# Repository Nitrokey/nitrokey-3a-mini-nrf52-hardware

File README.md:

# Nitrokey 3A Mini and Nitrokey Passkey Hardware

The hardware files of [Nitrokey 3A Mini](https://shop.nitrokey.com/shop/nk3am-nitrokey-3a-mini-149) and [Nitrokey Passkey](https://shop.nitrokey.com/shop/nkpk-nitrokey-passkey-418).
The firmware is [here](https://github.com/Nitrokey/nitrokey-3-firmware).

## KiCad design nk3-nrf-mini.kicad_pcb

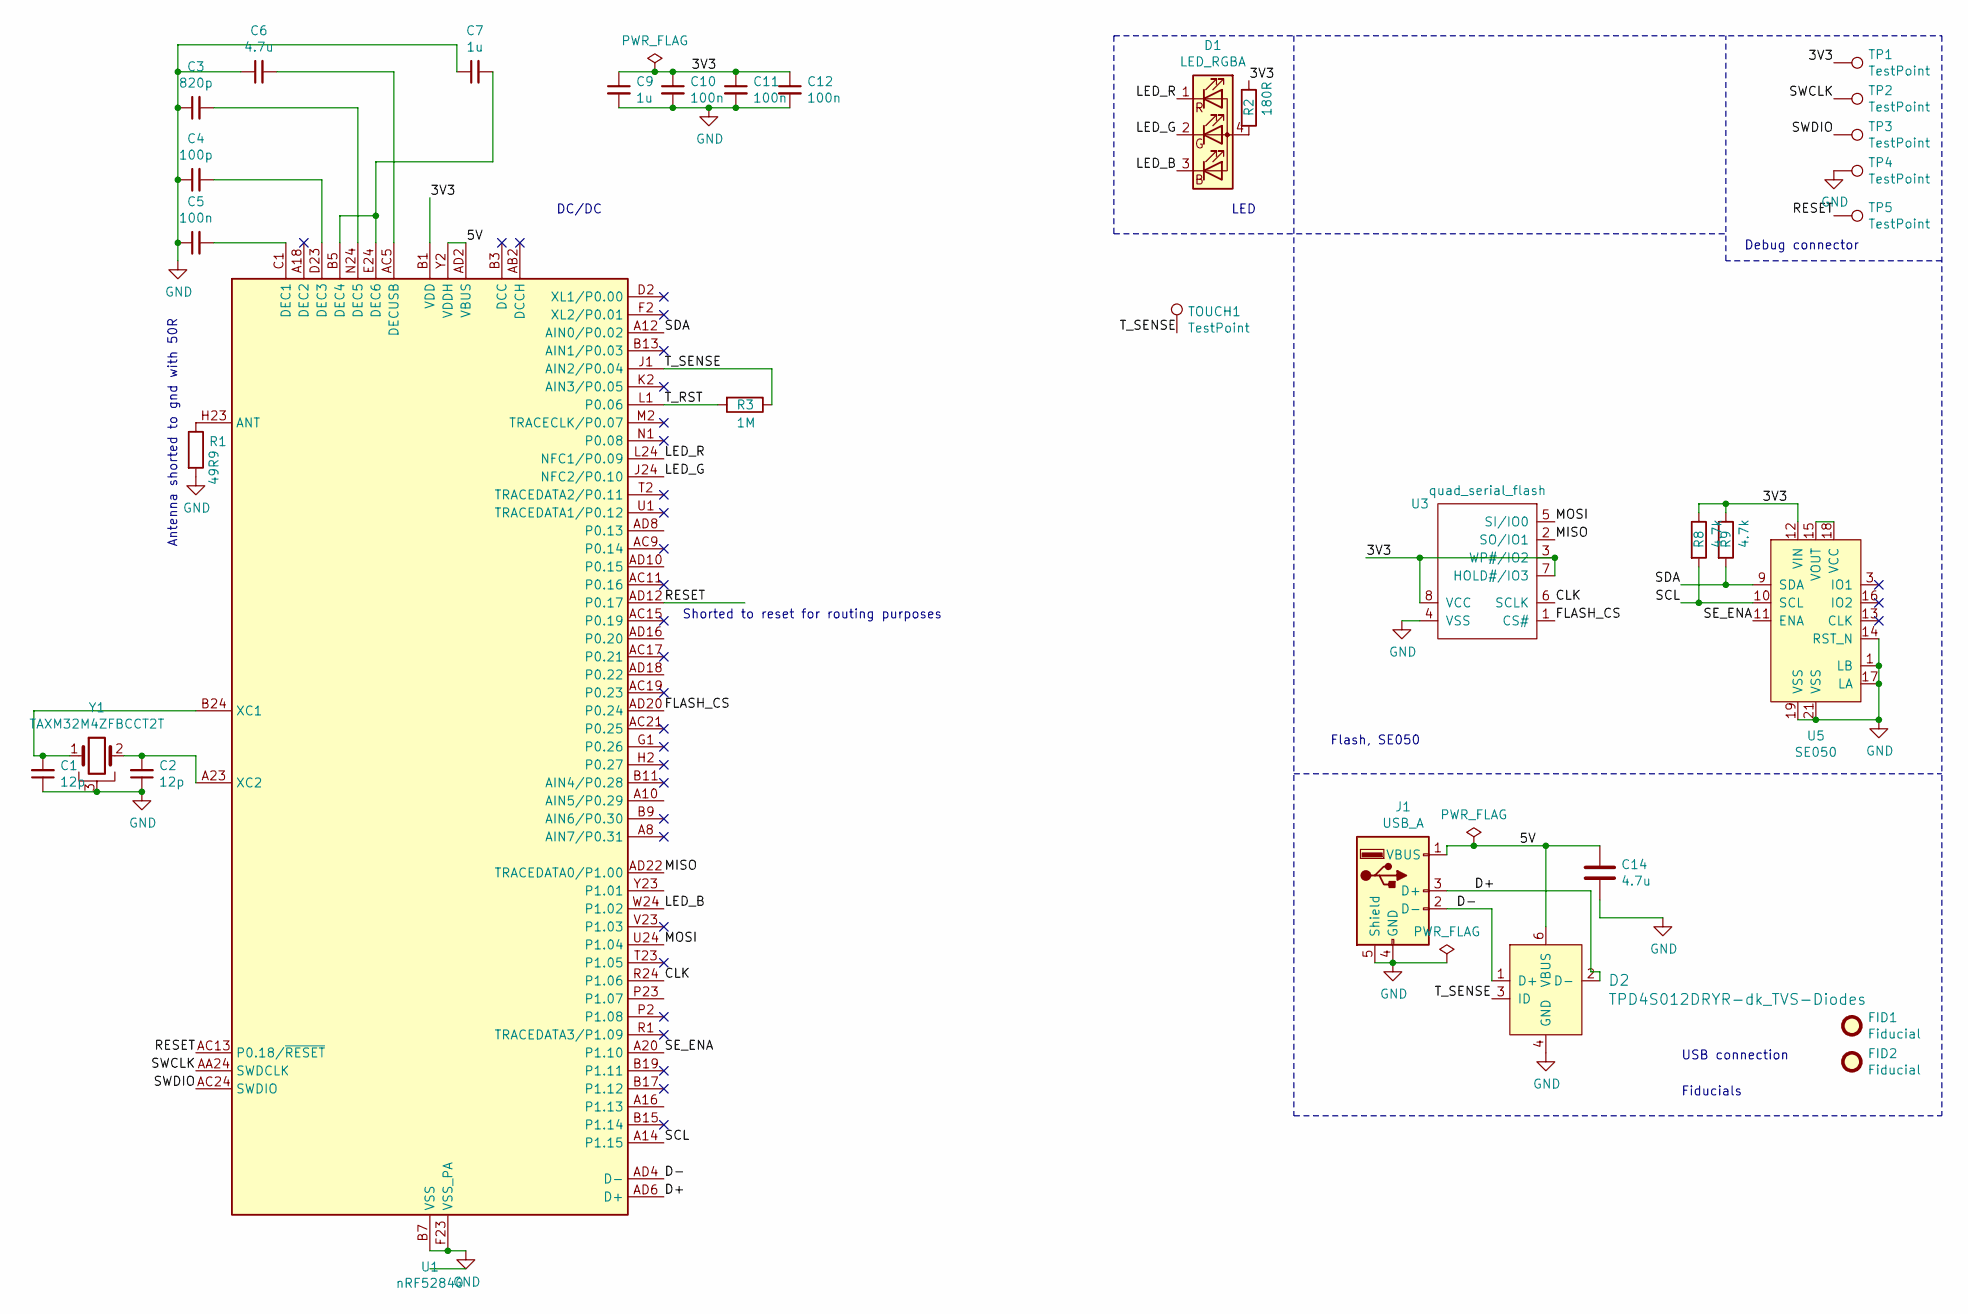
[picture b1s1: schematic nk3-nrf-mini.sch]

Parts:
C1, C2: 12p; C_0201_0603Metric
C3: 820p; C_0201_0603Metric
C4: 100p; C_0201_0603Metric
C5, C10, C11, C12: 100n; C_0201_0603Metric
C6, C14: 4.7u; C_0402_1005Metric
C7, C9: 1u; C_0402_1005Metric
D1: LED_RGBA; RGB_LED_606
D2: TPD4S012DRYR-dk_TVS-Diodes; UFDFN-6_1.45x1mm; MPN TPD4S012DRYR; Digi-Key_PN 296-24244-1-ND
FID1, FID2: Fiducial; Fiducial_0.5mm_Mask1mm
J1: USB_A; usb-a-pattern
R1: 49R9; R_0201_0603Metric
R2: 180R; R_0201_0603Metric
R3: 1M; R_0201_0603Metric
R8, R9: 4.7k; R_0201_0603Metric
TOUCH1: TestPoint; touchpad-curve
TP1, TP2, TP3, TP4, TP5: TestPoint; TestPoint_Pad_D1.5mm
U1: nRF52840; Nordic_AQFN-73-1EP_7x7mm_P0.5mm
U3: quad_serial_flash; FLASH_2x3_USON8
U5: SE050; UQFN-20-1EP_3x3mm_P0.4mm_EP1.85x1.85mm
Y1: TAXM32M4ZFBCCT2T; Crystal-2mmx1.6mm

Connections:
/3V3: C9.1, C10.1, C11.1, C12.1, R2.1, R8.1, R9.1, TP1.1, U1.A22 (VDD), U1.AD14 (VDD), U1.AD23 (VDD), U1.B1 (VDD), U1.W1 (VDD), U3.3 (WP#/IO2), U3.7 (HOLD#/IO3), U3.8 (VCC), U5.12 (VIN)
/5V: C14.1, D2.6 (VBUS), J1.1 (VBUS), U1.AD2 (VBUS), U1.Y2 (VDDH)
/CLK: U1.R24 (P1.06), U3.6 (SCLK)
/D+: D2.2 (D-), J1.3 (D+), U1.AD6 (D+)
/D-: D2.1 (D+), J1.2 (D-), U1.AD4 (D-)
/FLASH_CS: U1.AD20 (P0.24), U3.1 (CS#)
/LED_B: D1.3 (BK), U1.W24 (P1.02)
/LED_G: D1.2 (GK), U1.J24 (NFC2/P0.10)
/LED_R: D1.1 (RK), U1.L24 (NFC1/P0.09)
/MISO: U1.AD22 (TRACEDATA0/P1.00), U3.2 (SO/IO1)
/MOSI: U1.U24 (P1.04), U3.5 (SI/IO0)
/RESET: TP5.1, U1.AC13 (P0.18/~RESET), U1.AD12 (P0.17)
/SCL: R8.2, U1.A14 (P1.15), U5.10 (SCL)
/SDA: R9.2, U1.A12 (AIN0/P0.02), U5.9 (SDA)
/SE_ENA: U1.A20 (P1.10), U5.11 (ENA)
/SWCLK: TP2.1, U1.AA24 (SWDCLK)
/SWDIO: TP3.1, U1.AC24 (SWDIO)
/T_RST: R3.2, U1.L1 (P0.06)
/T_SENSE: D2.3 (ID), R3.1, TOUCH1.1, U1.J1 (AIN2/P0.04)
GND: C1.1, C2.1, C3.1, C4.1, C5.1, C6.1, C7.1, C9.2, C10.2, C11.2, C12.2, C14.2, D2.4 (GND), J1.4 (GND), J1.5 (Shield), R1.2, TP4.1, U1.B7 (VSS), U1.EP (VSS), U1.F23 (VSS_PA), U3.4 (VSS), U5.1 (LB), U5.14 (RST_N), U5.17 (LA), U5.19 (VSS), U5.21 (VSS), Y1.3
unnamed: C1.2, U1.B24 (XC1), Y1.1
unnamed: C2.2, U1.A23 (XC2), Y1.2
unnamed: C3.2, U1.N24 (DEC5)
unnamed: C4.2, U1.D23 (DEC3)
unnamed: C5.2, U1.C1 (DEC1)
unnamed: C6.2, U1.AC5 (DECUSB)
unnamed: C7.2, U1.B5 (DEC4), U1.E24 (DEC6)
unnamed: D1.4 (A), R2.2
unnamed: R1.1, U1.H23 (ANT)
unnamed: U5.15 (VOUT), U5.18 (VCC)

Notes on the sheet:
Flash, SE050
Debug connector
USB connection
LED
Antenna shorted to gnd with 50R
DC/DC
Fiducials
Shorted to reset for routing purposes

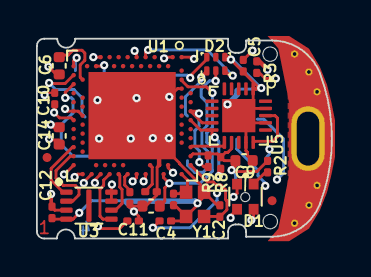
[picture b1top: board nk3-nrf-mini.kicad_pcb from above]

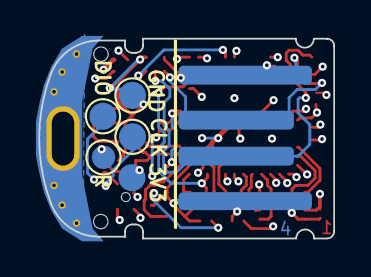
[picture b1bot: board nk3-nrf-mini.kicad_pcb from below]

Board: 4 copper layers, 16.4 x 11.1 mm, 32 parts (7 on the bottom side), 30 nets.

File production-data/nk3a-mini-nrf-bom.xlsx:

Component | Description | Part | References | Value | Footprint | Quantity Per PCB | MPN | Manufacturer
1 | C0G cap | C | C1 C2 | 12pF | C_0201_0603Metric | 2
2 | C0G cap | C | C3 | 820pF | C_0201_0603Metric | 1
3 | X5R or X7R cap, 25V | C | C5 C10 C11 C12 | 100nF | C_0201_0603Metric | 4
4 | X5R or X7R cap, 25V | C | C7 C9 | 1u | C_0402_1005Metric | 2
5 | X5R or X7R cap, 10V | C | C6 C14 | 4.7u | C_0402_1005Metric | 2
6 | C0G cap | C | C4 | 100pF | C_0201_0603Metric | 1
7 | TVS Diode | tvs diode | D2 | TPD4S012DRYR | UFDFN-6_1.45x1mm | 1 | TPD4S012DRYR | Texas Instruments
8 | SPI flash IC | spi flash | U3 | GD25Q16CEIGR | FLASH_2x3_USON8 | 1 | GD25Q16CEIGR | GigaDevice Semiconductor (HK) Limited
9 | RGB LED, red/green/blue/anode | LED_RGBA | D1 | LED_RGBA | RGB_LED_606 | 1 | 150066M153000 | Würth
10 | Resistor 1% | R | R1 | 49R9 | R_0201_0603Metric | 1
11 | Resistor 1% | R | R2 | 180R | R_0201_0603Metric | 1
12 | Resistor 1% | R | R3 | 1M | R_0201_0603Metric | 1
13 | Resistor 1% | R | R8 R9 | 4.7k | R_0201_0603Metric | 2
14 | Secure element | SE050 | U5 | SE050 | UQFN-20-1EP_3x3mm_P0.4mm_EP1.85x1.85mm | 1 | SE050C1HQ1/Z01SCZ | NXP
15 | Crystal | Crystal | Y1 | TAXM32M4ZFBCCT2T | Crystal-2mmx1.6mm | 1 | TAXM32M4ZFBCCT2T | TAE
16 | nRF52840 microcontroller | NRF52840-QIAA-R | U1 | NRF52840-QIAA-R | Nordic_AQFN-73-1EP_7x7mm_P0.5mm | 1 | NRF52840-QIAA-R | Nordic Semiconductor ASA

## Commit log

2026-04-24 nk3am121+122
2026-04-24 add README.md
    Add documentation for Nitrokey 3A Mini and Passkey hardware.
2026-04-24 nk3am122+123
